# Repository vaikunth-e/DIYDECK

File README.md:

# DIYDECK: STM32 Audio Effects Processor with Custom PCB

DIYDECK is a custom audio-processing board/system that takes an external audio signal, conditions it for an STM32 ADC, applies real-time embedded DSP effects, and outputs the processed signal through the STM32 DAC into the audio board/amplifier path.

[Demo](https://youtu.be/CMMS7bL4tLE)

## Features

- STM32 Nucleo-F303RE firmware using PlatformIO
- Real-time ADC-to-DAC audio passthrough
- Timer-driven sampling using TIM3
- Freeverb-style reverb
- Ring modulation
- Rotary encoder control for PWM-selected filter settings
- Mute switch and button-controlled effects
- Custom KiCad PCB files included

## System overview

Input audio is AC-coupled and biased around mid-supply so the STM32 ADC can sample the waveform safely. The firmware removes the measured DC bias, applies optional effects, recenters the signal around the DAC midpoint, and outputs it through DAC channel 1.

Signal chain:

Laptop / audio source  
→ AC coupling and biasing  
→ STM32 ADC input  
→ real-time DSP  
→ STM32 DAC output  
→ PCB audio path / amplifier / speaker

## Hardware

- STM32 Nucleo-F303RE
- ADC input: A0 / PA0 / ADC1_IN1
- DAC output: A2 / PA4 / DAC_OUT1
- Rotary encoder for filter selection
- Effect buttons for reverb and ring modulation
- Mute switch
- Custom PCB designed in KiCad

## Firmware architecture

- `src/main.cpp`: ADC/DAC setup, audio ISR, effect toggles, timer setup
- `src/encoder_control.cpp`: rotary encoder decoding and PWM setting selection
- `lib/my_reverb`: Freeverb-style reverb implementation
- `lib/my_ringmod`: ring modulation effect

## Audio processing

Each sample is read from the ADC, denoised slightly by masking noisy LSBs, centered by subtracting a moving DC estimate, optionally processed through reverb and/or ring modulation, clipped to the DAC range, and written to the DAC.

## Filter / PWM control

The rotary encoder selects one of 16 predefined cutoff settings. Each setting maps a target cutoff frequency to two PWM duty cycles used by the external board.

## Debugging and validation

During bring-up, I debugged DC offset, clipping, low output volume, scratchiness, sample-rate instability, and ADC/DAC scaling. I used serial diagnostics and lab equipment including an oscilloscope, multimeter, function generator, and bench power supply to validate the signal path.

## Known limitations

- Audio quality depends heavily on input biasing and gain staging
- Some sample rates produced more noise or unstable effect behavior
- Reverb quality is constrained by STM32 memory and real-time processing budget

## Build and upload

```bash
pio run
pio run --target upload
pio device monitor

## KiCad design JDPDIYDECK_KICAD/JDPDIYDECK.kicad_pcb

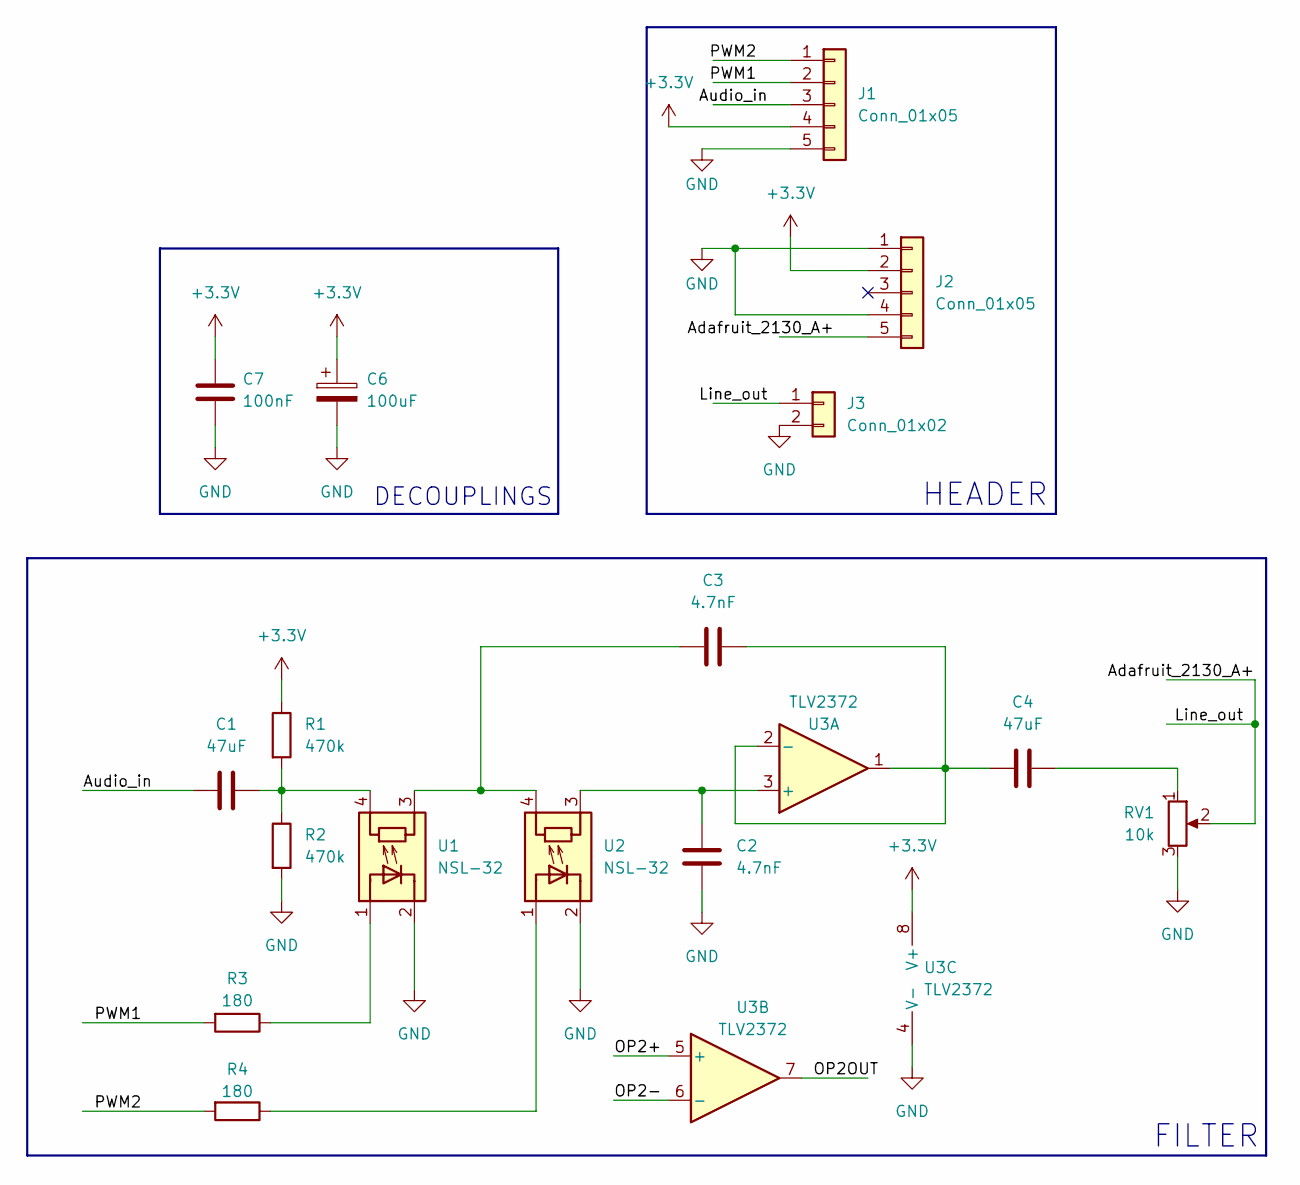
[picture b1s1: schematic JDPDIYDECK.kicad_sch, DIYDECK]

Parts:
C1, C4: 47uF; CAP_RDEC71E476MWK1H03B
C2, C3: 4.7nF; CAPRB500W50L400T250H550
C6: 100uF; CP_Radial_D5.0mm_P2.00mm
C7: 100nF; C_Rect_L4.0mm_W2.5mm_P2.50mm
J1: Conn_01x05; PinHeader_1x05_P2.54mm_Vertical
J2: Conn_01x05; PinSocket_1x05_P2.54mm_Vertical
J3: Conn_01x02; PinSocket_1x02_P2.54mm_Vertical
R1, R2: 470k; R_Axial_DIN0207_L6.3mm_D2.5mm_P10.16mm_Horizontal
R3, R4: 180; R_Axial_DIN0207_L6.3mm_D2.5mm_P10.16mm_Horizontal
RV1: 10k; Potentiometer_Bourns_PTV09A-1_Single_Vertical
U1, U2: NSL-32; Luna_NSL-32
U3: TLV2372; P8

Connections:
+3.3V: C6.1, C7.1, J1.4, J2.2, R1.1, U3.8 (V+)
/Adafruit_2130_A+: J2.5, J3.1, RV1.2
/Audio_in: C1.1, J1.3
/OP2+: U3.5 (+)
/OP2-: U3.6 (-)
/OP2OUT: U3.7
/PWM1: J1.2, R3.2
/PWM2: J1.1, R4.2
GND: C2.2, C6.2, C7.2, J1.5, J2.1, J2.4, J3.2, R2.2, RV1.3, U1.2 (K), U2.2 (K), U3.4 (V-)
unnamed: C1.2, R1.2, R2.1, U1.4 (R)
unnamed: C3.2, U1.3 (R), U2.4 (R)
unnamed: C4.2, RV1.1
unnamed: R3.1, U1.1 (A)
unnamed: R4.1, U2.1 (A)
unnamed: C2.1, U2.3 (R), U3.3 (+)
unnamed: C3.1, C4.1, U3.1, U3.2 (-)

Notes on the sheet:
HEADER
DECOUPLINGS
FILTER

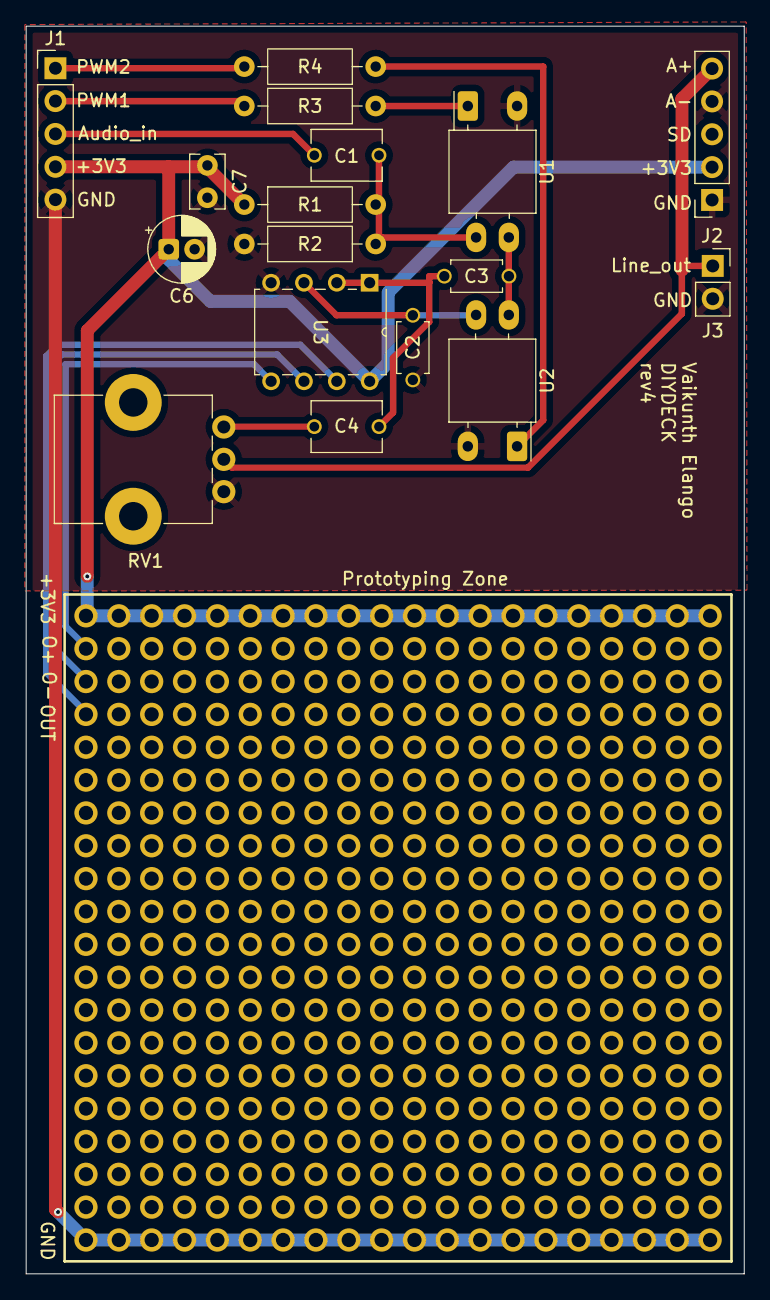
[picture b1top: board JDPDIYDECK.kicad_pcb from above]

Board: 2 copper layers, 55.5 x 96.5 mm, 17 parts (0 on the bottom side), 13 nets.

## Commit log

2026-04-25 passthrough functional
2026-05-06 reverb functionality
2026-05-11 encoder
2026-05-12 Add initial project title to README
2026-05-15 Enhance README with project details and instructions
    Expanded README with detailed project information, features, hardware setup, firmware architecture, audio processing, and debugging insights.
2026-05-16 amendments to op amp routing
